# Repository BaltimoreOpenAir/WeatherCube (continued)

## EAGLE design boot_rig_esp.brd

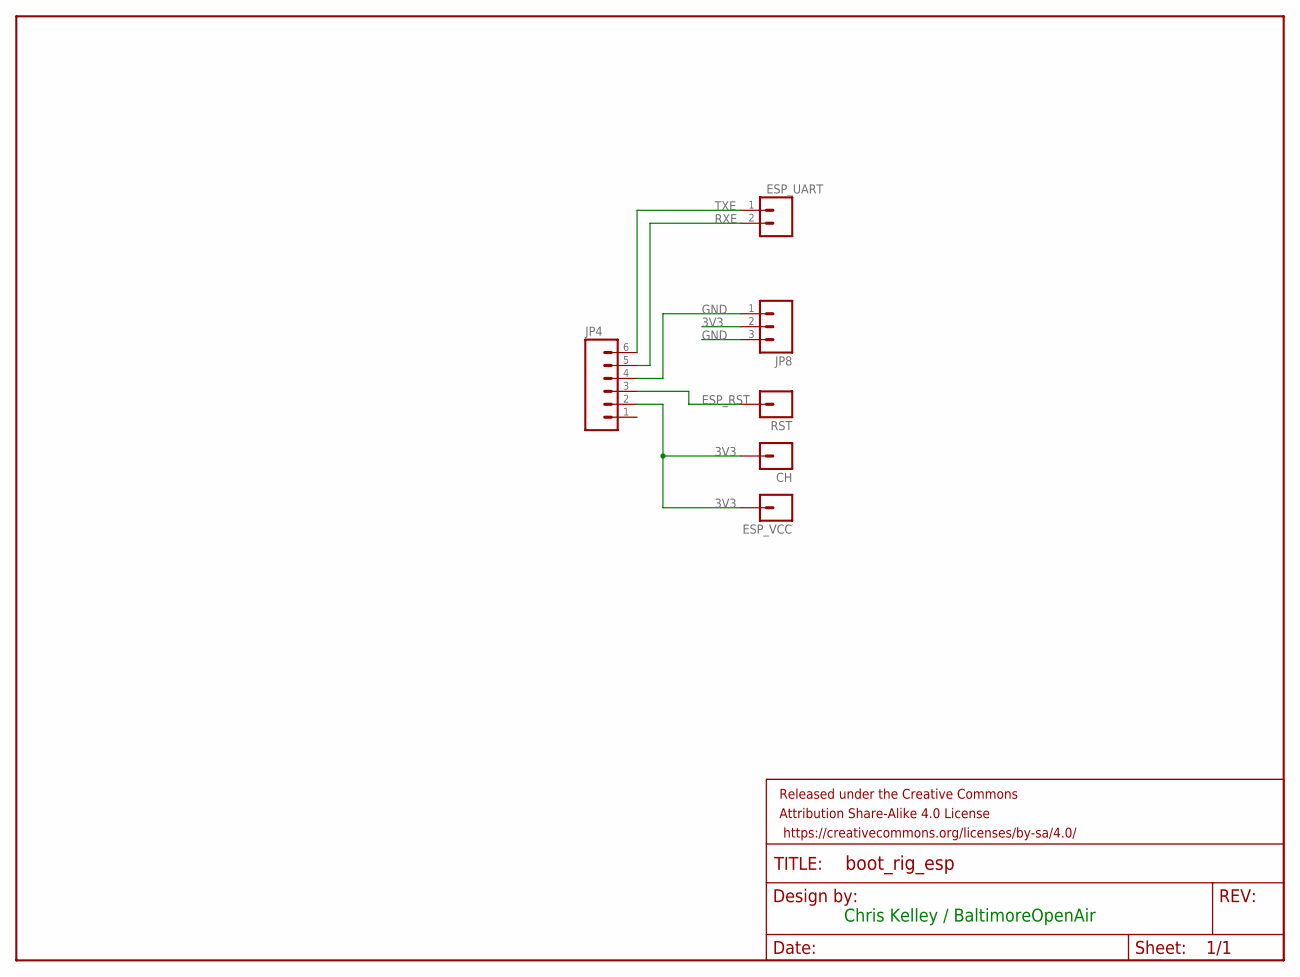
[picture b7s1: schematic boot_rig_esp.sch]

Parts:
CH: M01PTH; 1X01
ESP_UART: M02PTH; 1X02
ESP_VCC: M01PTH; 1X01
FRAME1: FRAME-LETTER; CREATIVE_COMMONS
JP4: M06SILK_FEMALE_PTH; 1X06
JP8: M03PTH; 1X03
RST: M01PTH; 1X01

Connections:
3V3: CH.1, ESP_VCC.1, JP4.2, JP8.2
ESP_RST: JP4.3, RST.1
GND: JP4.4, JP8.1, JP8.3
RXE: ESP_UART.2, JP4.5
TXE: ESP_UART.1, JP4.6

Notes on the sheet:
Chris Kelley / BaltimoreOpenAir

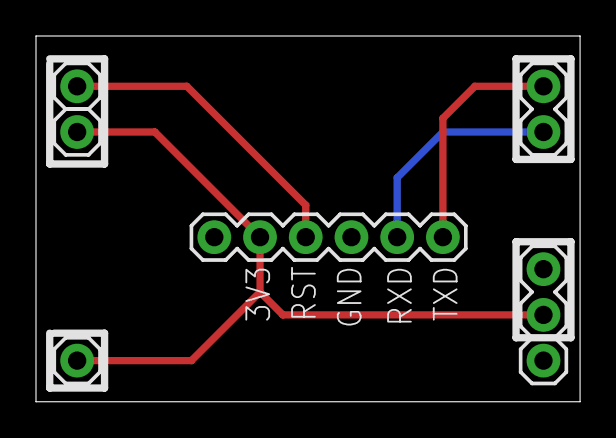
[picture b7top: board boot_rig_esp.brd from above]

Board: 2 copper layers, 30.2 x 20.3 mm, 7 parts (0 on the bottom side), 5 nets.

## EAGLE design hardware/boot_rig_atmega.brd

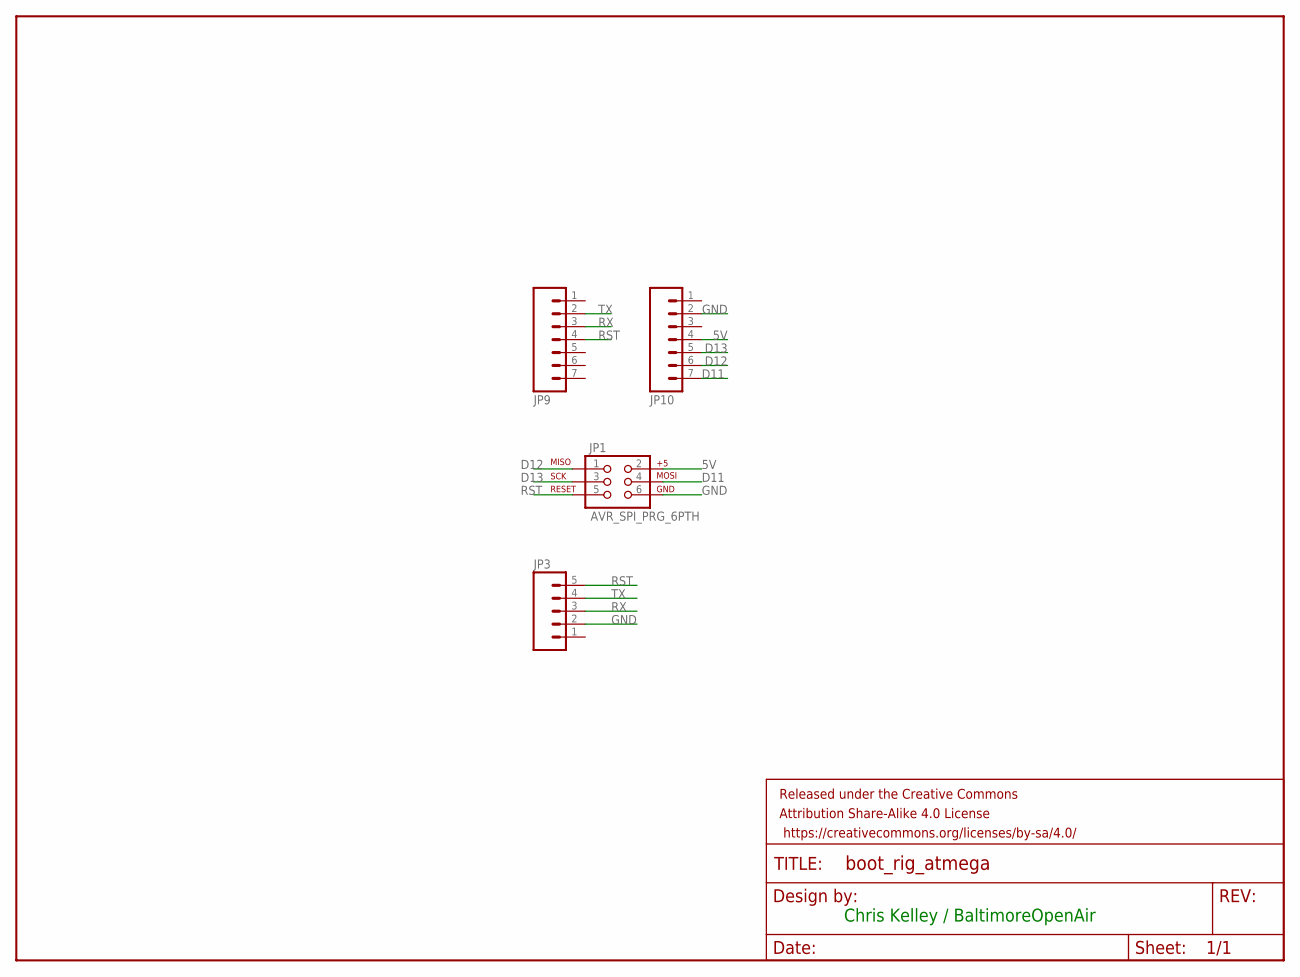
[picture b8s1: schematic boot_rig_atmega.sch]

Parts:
FRAME1: FRAME-LETTER; CREATIVE_COMMONS
JP1: AVR_SPI_PRG_6PTH; 2X3
JP3: M05PTH; 1X05
JP9, JP10: M07; 1X07

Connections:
5V: JP1.2, JP3.1, JP10.4
D11: JP1.4, JP10.7
D12: JP1.1, JP10.6
D13: JP1.3, JP10.5
GND: JP1.6, JP3.2, JP10.2
RST: JP1.5, JP3.5, JP9.4
RX: JP3.3, JP9.3
TX: JP3.4, JP9.2

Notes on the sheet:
Chris Kelley / BaltimoreOpenAir

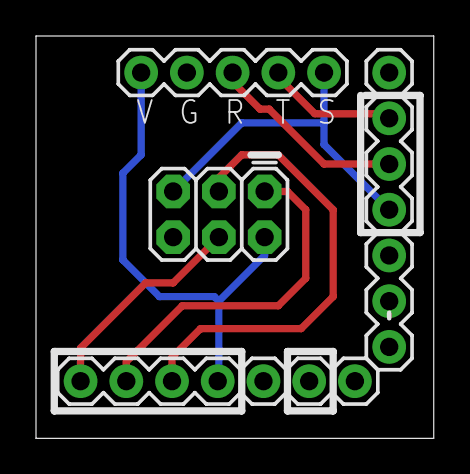
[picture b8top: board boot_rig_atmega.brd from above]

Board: 2 copper layers, 22.1 x 22.4 mm, 5 parts (0 on the bottom side), 8 nets.

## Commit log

2017-08-04 eeprom readout after writing in debug mode fixed
2017-08-05 starting to add wifi code
2017-08-07 sends a char array from atmega to esp to aws
2017-08-08 rewrite of esp_main.ino
    Ready to connect to the atm_main.ino. Communications passed to the esp by the atmega are used to communicate a parameter datum, send a post consisting of a collection of parameter data, or query the 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
    Acceptable communications to the ESP (see lines 113 - 139) are of the format [t 23.45x] where 't' is the command character (in this case, set the temperature value), followed by a space, then up to 2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
2017-08-08 added test post function for debug mode
    (this is anna on Yan's account)
2017-08-08 adding read and send functionality
2017-08-09 posting messages to AWS w/ send_dummy_message
2017-08-09 uploading data to temp field
2017-08-09 testing of posting a dummy message
2017-08-09 working example
2017-08-10 can send strings from atmega to aws
2017-08-10 reads #'s from eeprom and sends to aws success
2017-08-10 clean code, uploads to aws
2017-08-10 added double EEPROM read/write functions
2017-08-10 working
2017-08-10 working code committing data to aws
2017-08-10 Working example reads, writes, posts
2017-08-10 accept negative numbers in bit-shifted saving
2017-08-10 bit shifted write/read eeprom working
2017-08-11 Posting most of the data string to Dynamo db
    Esp-main on esp, wxcube main on atmega.
2017-08-15 rewrote loop counter & messages send one at a time
2017-08-17 may not be compiling
2017-08-19 adding circuit board files
    three WeatherCube circuit boards, plus two boot rig boards; EagleCAD schematic and board layout files for each
2017-08-19 reading/writing from correct locations
2017-08-20 posting category data to dynamodb
2017-08-22 added test post & post confirmation
2017-08-22 fixed intervals, still having issues reading data?
2017-08-22 fixed sensor saving
    Still getting nans in some stds and the thermometers
2017-08-26 added deep sleep mode
2017-08-27 uploading data, but also zeros
2017-08-27 added verbose option to script
2017-08-29 uploading hourly to AWS
    also added 10 tries for wifi posting, still need to take care of case where there is partial posting
2017-09-06 corrected voltage, fixed temp readings, etc
2017-09-06 (anna again) continuous measurements
2017-09-06 fixed initial loop counter saving
2017-09-14 reorganized hardware and software
2017-09-14 Create LICENSE
    Added hardware license
2017-09-14 Update LICENSE
2017-09-14 adding CC BY-NC-SA 4.0 license
2018-01-31 fall code update
2018-01-31 adding fix for vref + Chris code cleanup
2018-01-31 removing weights for AQ readings
2018-02-18 making git file directory openable in arduino
2018-02-18 added zonda modifications, untested
2018-03-03 added zonda code
2018-03-03 added PMS demo code
2018-03-03 Update zonda.ino
    added reminder about writing hour and seconds to data
2018-03-03 turned on vref and got then output syncing
2018-03-03 added PM sensor code
2018-03-05 images for readme
2018-03-10 syncing code
2018-03-10 removed commented code
2018-03-21 Update zonda.ino
    Fixed buffer overflow, increased available RAM. Should be ready for field use.
2018-03-23 Added F macros to some print statements, moved two errant brackets
2018-03-23 Added missing close paren
2018-04-02 uncommmented read data code
2018-04-04 adding aws instructions
2018-04-14 uncommented send data
2018-04-14 continuous measurement and data sending
2018-04-14 changed loop_counter to restart at 0
2018-04-14 updated LMP91000 init and leave VREF_EN high
2018-04-14 cleaning up repo
2018-04-18 changed loop counter to 1
    # Conflicts:
    # software/wxcube_main/wxcube_dev_chris.ino
2018-04-18 uncommented sleep and send code
2018-04-20 refactored zonda, removed unnecessary wxcube code
2018-04-23 fixed bug with while condition on line 256
2018-04-23 Fixed "Exception(28)..." issue
2018-04-30 minor updates
2018-05-01 Edits to match ESP firmware / SS edits
2018-05-01 Create esp_main_hardcoded
2018-06-08 starting powertrain
2018-07-12 board updates
